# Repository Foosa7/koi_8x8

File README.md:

# Koi 8×8 — 64-channel current-source driver / readout

An open-hardware, low-cost controller for driving **TiN thermo-optic heaters on
photonic chips**: 64 independent precision current sources with per-channel
voltage readback, built from one controller board and eight hot-pluggable
8-channel analog boards.

Each daughterboard pairs a 16-bit DAC (DAC80508) with eight XTR200 precision
current sources, and reads the voltage across each load through a 6:1 divider
with a 24-bit ΔΣ ADC (AD7193), so the host gets current, voltage, resistance,
and power per channel. A Raspberry Pi Pico (RP2040) on the motherboard runs a
line-based ASCII command server over USB — one `ISETA` sets all 64 currents,
one `MEASA?` reads all 64 voltages.

## The boards

| [Motherboard](hardware/motherboard/) — RP2040 controller, 8 slots | [Daughterboard](hardware/daughterboard/) — 8 analog channels, ×8 |
| --- | --- |
|  |  |

Renders are regenerated from the KiCad boards with `kicad-cli pcb render`; each
board's own README has top, bottom, and transparent-background views.

## Key numbers

| Metric | Value |
| --- | --- |
| Channels | 64 (8 boards × 8), hot-pluggable per board |
| Current range | 0–6 mA per channel (working range 0.25–6 mA), 16-bit setting |
| Readback | 24-bit ΔΣ, divider-corrected load voltage → V / R / P per channel |
| Linearity (measured, 23 ch) | worst-case ±0.32 µA deviation from linear over 0.25–6 mA (≈0.006 % of span) |
| Offset (pre-calibration) | ≈24 µA systematic, uniform across channels; single-point cal brings it to the ±4 µA XTR200 device floor (Keithley campaign planned) |
| Full 64-channel scan | ≈11 ms/channel at the default filter rate (~0.7 s for all 64; filter rate adjustable live) |
| Parts cost | **$709 per system ≈ $11.08/channel** ([master_bom.csv](master_bom.csv)) — commercial equivalents (e.g. Qontrol) ≈ $125/channel |

## Measured results (3 boards / 24 channels, 2026-07-03)

| | |
| --- | --- |
|  |  |

Three populated daughterboards were swept 0.1–6 mA into nominal 820 Ω ±1 %
loads (one channel had no load fitted during the run and is excluded). All 23
loaded channels are linear to within ±0.32 µA and show a uniform ~24 µA
pre-calibration offset — a systematic that the planned per-channel calibration
removes. Figures are regenerated from the raw bench CSVs by
`report/figures/make_figures.py`.

## What's in this folder

| Path | Contents |
| --- | --- |
| `report/figures/` | Architecture diagram + measurement figures (and the scripts that generate them) |
| `hardware/motherboard/` | KiCad project, schematic PDF (`Schematics/`), power-tree spec (`POWER.md`), top/bottom/transparent renders, fab outputs (`production/`: gerbers, BOM, positions) |
| `hardware/daughterboard/` | Same set for the analog board, plus an interactive HTML BOM (`bom/ibom.html`) |
| `hardware/render/` | Headless KiCad → pcb2blender → Cycles pipeline for photorealistic board renders |
| `master_bom.csv` | Consolidated system BOM with unit prices and cost total |
| `firmware/motherboard-test/` | RP2040 firmware (PlatformIO, `pio run -t upload`) and Python host tools — `tools/koi_gui.py` is a live 8×8 monitor GUI; `tools/*.csv` are the raw bench datasets |
| `paper/main.pdf` | Draft HardwareX manuscript (validation section pending the calibration campaign) |

## Status (August 2026)

**In fab:** both revised boards were released to fabrication on **2026-08-12**.
The motherboard adds the protected input stage (PPTC + SMBJ16A TVS + P-FET
reverse-polarity with a BZT52C18 gate clamp), the 12 → 5 → 3.3 V tree with the
`3V3_EN` interlock, a +12 V sense divider into `GPIO26`, and the `U3.~OE`
cutover to `GPIO19`; the daughterboard adds the OPA2333 followers (U13–U16) and
their 1 kΩ series resistors. `hardware/*/production/` holds the exact gerber /
BOM / position sets that were sent.

**Done:** rev-1 hardware designed, fabricated, and brought up; firmware 1.1
with robust host protocol (auto-detection, hot-rescan, fast scanning); host GUI
and calibration tooling; all 8 daughterboards populated and tested (initial
3-board/24-channel results above — production sign-off).

**Resolved:** the ~3 mV offset seen during the 8-board test was the AD7193's
*internal* input buffer. With the 6:1 divider, a low-current channel's ADC input
sits below the buffered mode's usable common-mode range, so the buffer added a
systematic offset rather than tracking. Fixed by disabling it (`CONF.BUF = 0`)
and adding 8 external unity-gain **OPA2333** followers (U13–U16) between the
divider taps and the ADC inputs.

**Next:** Keithley 2400/2100 per-channel calibration campaign (jig designed,
parts list ready); HardwareX submission.

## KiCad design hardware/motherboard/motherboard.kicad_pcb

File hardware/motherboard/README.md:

# Motherboard — RP2040 controller board

The controller board for Koi 8×8. Carries a Raspberry Pi Pico (RP2040) and
hosts up to 8 [daughterboards](../daughterboard/) in PCIe-x4 card-edge slots,
addressing each board's DAC/ADC over a shared SPI bus. Formerly codenamed
`MOBO`. The PC talks to the Pico's firmware over USB serial — see
[`firmware/motherboard-test/`](../../firmware/motherboard-test/).

| Top | Bottom |
| --- | --- |
|  |  |

Same top view with an alpha background, for dropping onto slides or into the
paper's figures:

## What's on it

| Ref | Part | Function |
| --- | --- | --- |
| A1 | Raspberry Pi Pico (RP2040) | Runs the firmware; USB-serial host link |
| U1, U5 | SN74LV138 (74HC138) | 3-to-8 decoders — ADC/DAC chip-select across the 8 slots |
| U3 | SN74LV595 | Shift register — XTR200 front-end enables |
| U2 | TMUX1208PW | 8:1 analog mux |
| J1–J8 | Samtec PCIE-064-02-F-D-TH | 8 daughterboard slots (PCIe-x4 sockets) |
| J9–J11 | Molex 54132-5033 | 50-pin FFC connectors — channel outputs |

### Power tree

The barrel jack is the only power source; the Pico is a peripheral that cannot
run without it, enforced in hardware by the `3V3_EN` interlock (R7/R8) rather
than in firmware. Full design rationale: [`POWER.md`](POWER.md).

| Ref | Part | Function |
| --- | --- | --- |
| J12 | Barrel jack + switch pin | DC power in, 9–15 V |
| F1 | 1812L150/24MR polyfuse | Input overcurrent protection |
| D2 | SMBJ16A | Input TVS clamp (26 V clamping voltage) |
| Q1 | AO3407A | P-FET reverse-polarity protection |
| D6 | BZT52C18 | `Q1` gate–source clamp |
| U6 | K7805-500R3 | 5 V switching regulator |
| U4 | LP5912-3.3DRV | 3.3 V LDO — logic rail and daughterboard `+3V3` |
| D1 | SS34 | Feeds the Pico's VSYS from the board's 5 V rail |
| R7, R8 | 10 kΩ / 4.7 kΩ | `3V3_EN` interlock divider |
| R5, R10, C10 | 100 kΩ / 22 kΩ / 100 nF | +12 V sense divider into `GPIO26`/ADC0 (×5.5455) |

Full pricing and part numbers: [`../../master_bom.csv`](../../master_bom.csv).

## Files

| File | What it is |
| --- | --- |
| `motherboard.kicad_pro` / `.kicad_sch` / `.kicad_pcb` | The KiCad project |
| `Schematics/motherboard.pdf` | Exported schematic |
| `production/` | Fab outputs — gerbers, BOM, positions, netlist |
| `POWER.md` | Power-tree design spec — input protection chain and the `3V3_EN` interlock |
| `motherboard*.png` | Board views above, regenerated with `kicad-cli pcb render` |
| `PCIE-064-02-F-D-TH.stp`, `Pico.wrl` | 3D models used for the renders above |

Photorealistic Cycles renders (`motherboard_render*.png`) are produced by the
pipeline in [`../render/`](../render/) — not generated yet.

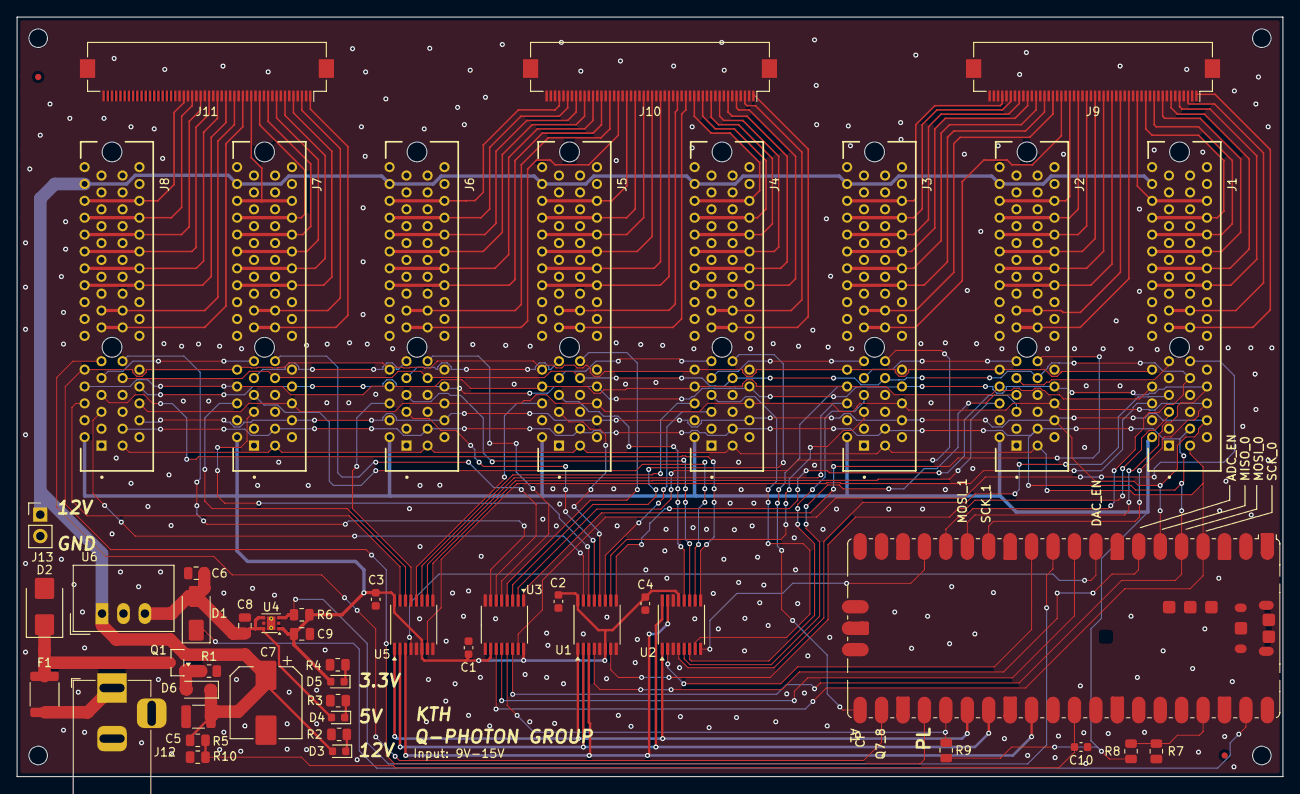
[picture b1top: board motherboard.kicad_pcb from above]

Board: 4 copper layers, 150.0 x 90.0 mm, 50 parts (0 on the bottom side), 135 nets.

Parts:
A1: RaspberryPi_Pico; RaspberryPi_Pico_SMD
C1, C2, C3, C4, C10: 0.1uF; C_0603_1608Metric
C5: 10uF; C_1210_3225Metric
C6: 22uF; C_0805_2012Metric
C7: 220uF; CP_Elec_8x10
C8, C9: 10uF; C_0805_2012Metric
D1: SS34; D_SMA
D2: SMBJ16A; D_SMB
D3, D4, D5: LED; LED_0603_1608Metric
D6: BZT52C18; D_SOD-123
F1: 1812L150/24MR; Fuse_1812_4532Metric
FID1, FID2: Fiducial; Fiducial_0.75mm_Mask1.5mm
J1, J2, J3, J4, J5, J6, J7, J8: PCIE-064-02-F-D-TH; SAMTEC_PCIE-064-02-X-D-TH
J9, J10, J11: Conn_01x50_MountingPin; Hirose_FH12-50S-0.5SH_1x50-1MP_P0.50mm_Horizontal
J12: Barrel_Jack_Switch_Pin3Ring; BarrelJack_Horizontal
J13: Conn_01x02_Pin; PinHeader_1x02_P2.54mm_Vertical
Q1: AO3407A; SOT-23
R1, R5, R6: 100k; R_0805_2012Metric
R2, R8: 4.7k; R_0805_2012Metric
R3: 1.5k; R_0805_2012Metric
R4: 680; R_0805_2012Metric
R7, R9: 10k; R_0805_2012Metric
R10: 22k; R_0805_2012Metric
U1, U5: SN74HC138PWR; TSSOP-16_4.4x5mm_P0.65mm
U2: TMUX1208PW; TSSOP-16_4.4x5mm_P0.65mm
U3: SN74LV595; TSSOP-16_4.4x5mm_P0.65mm
U4: LP5912-3.3DRV; WSON-6-1EP_2x2mm_P0.65mm_EP1x1.6mm_ThermalVias
U6: K7805-500R3; Converter_DCDC_TRACO_TSR-1_THT

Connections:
3V3_EN: A1.37 (3V3_EN), R7.2, R8.1
12V_SENSE: A1.31 (GPIO26_ADC0), C10.1, R5.2, R10.1
+3.3V: C1.1, C2.1, C3.1, C4.1, C9.1, D5.2 (A), J1.A2 (+3.3V), J2.A2 (+3.3V), J3.A2 (+3.3V), J4.A2 (+3.3V), J5.A2 (+3.3V), J6.A2 (+3.3V), J7.A2 (+3.3V), J8.A2 (+3.3V), R6.1, R8.2, R9.2, U1.6 (E2), U1.16 (VCC), U2.13 (VDD), U3.10 (~SRCLR), U3.16 (VCC), U4.1 (OUT), U5.6 (E2), U5.16 (VCC)
+5V: C6.1, C8.1, D1.2 (A), D4.2 (A), U4.4 (EN), U4.6 (IN), U6.3 (Vout)
+12V: C5.1, C7.1, D3.2 (A), D6.1 (K), J1.A30 (+12V), J2.A30 (+12V), J3.A30 (+12V), J4.A30 (+12V), J5.A30 (+12V), J6.A30 (+12V), J7.A30 (+12V), J8.A30 (+12V), J13.1, Q1.2 (S), R5.1, U6.1 (Vin)
A1: A1.26 (GPIO20), U1.1 (A0), U2.1 (A0), U5.1 (A0)
A2: A1.27 (GPIO21), U1.2 (A1), U2.16 (A1), U5.2 (A1)
A3: A1.29 (GPIO22), U1.3 (A2), U2.15 (A2), U5.3 (A2)
ADC_CS1: J1.A5 (ADC_CS), U1.7 (~Y7)
ADC_CS2: J2.A5 (ADC_CS), U1.9 (~Y6)
ADC_CS3: J3.A5 (ADC_CS), U1.10 (~Y5)
ADC_CS4: J4.A5 (ADC_CS), U1.11 (~Y4)
ADC_CS5: J5.A5 (ADC_CS), U1.12 (~Y3)
ADC_CS6: J6.A5 (ADC_CS), U1.13 (~Y2)
ADC_CS7: J7.A5 (ADC_CS), U1.14 (~Y1)
ADC_CS8: J8.A5 (ADC_CS), U1.15 (~Y0)
ADC_EN: A1.7 (GPIO5), U1.4 (~E0)
AT1: J1.A7 (AT), U2.4 (S1)
AT2: J2.A7 (AT), U2.5 (S2)
AT3: J3.A7 (AT), U2.6 (S3)
AT4: J4.A7 (AT), U2.7 (S4)
AT5: J5.A7 (AT), U2.12 (S5)
AT6: J6.A7 (AT), U2.11 (S6)
AT7: J7.A7 (AT), U2.10 (S7)
AT8: J8.A7 (AT), U2.9 (S8)
AT_EN: A1.12 (GPIO9), U2.2 (EN)
AT_MUX: A1.17 (GPIO13), U2.8 (D)
CH0: J1.A13 (CH0), J1.B13 (CH0), J9.1
CH1: J1.A15 (CH1), J1.B15 (CH1), J9.3
CH2: J1.A18 (CH2), J1.B18 (CH2), J9.5
CH3: J1.A20 (CH3), J1.B20 (CH3), J9.7
CH4: J1.A22 (CH4), J1.B22 (CH4), J9.9
CH5: J1.A24 (CH5), J1.B24 (CH5), J9.11
CH6: J1.A26 (CH6), J1.B26 (CH6), J9.13
CH7: J1.A28 (CH7), J1.B28 (CH7), J9.15
CH8: J2.A13 (CH0), J2.B13 (CH0), J9.17
CH9: J2.A15 (CH1), J2.B15 (CH1), J9.19
CH10: J2.A18 (CH2), J2.B18 (CH2), J9.21
CH11: J2.A20 (CH3), J2.B20 (CH3), J9.23
CH12: J2.A22 (CH4), J2.B22 (CH4), J9.25
CH13: J2.A24 (CH5), J2.B24 (CH5), J9.27
CH14: J2.A26 (CH6), J2.B26 (CH6), J9.29
CH15: J2.A28 (CH7), J2.B28 (CH7), J9.31
CH16: J3.A13 (CH0), J3.B13 (CH0), J9.33
CH17: J3.A15 (CH1), J3.B15 (CH1), J9.35
CH18: J3.A18 (CH2), J3.B18 (CH2), J9.37
CH19: J3.A20 (CH3), J3.B20 (CH3), J9.39
CH20: J3.A22 (CH4), J3.B22 (CH4), J9.41
CH21: J3.A24 (CH5), J3.B24 (CH5), J9.43
CH22: J3.A26 (CH6), J3.B26 (CH6), J9.45
CH23: J3.A28 (CH7), J3.B28 (CH7), J9.47
CH24: J4.A13 (CH0), J4.B13 (CH0), J10.1
CH25: J4.A15 (CH1), J4.B15 (CH1), J10.3
CH26: J4.A18 (CH2), J4.B18 (CH2), J10.5
CH27: J4.A20 (CH3), J4.B20 (CH3), J10.7
CH28: J4.A22 (CH4), J4.B22 (CH4), J10.9
CH29: J4.A24 (CH5), J4.B24 (CH5), J10.11
CH30: J4.A26 (CH6), J4.B26 (CH6), J10.13
CH31: J4.A28 (CH7), J4.B28 (CH7), J10.15
CH32: J5.A13 (CH0), J5.B13 (CH0), J10.17
CH33: J5.A15 (CH1), J5.B15 (CH1), J10.19
CH34: J5.A18 (CH2), J5.B18 (CH2), J10.21
CH35: J5.A20 (CH3), J5.B20 (CH3), J10.23
CH36: J5.A22 (CH4), J5.B22 (CH4), J10.25
CH37: J5.A24 (CH5), J5.B24 (CH5), J10.27
CH38: J5.A26 (CH6), J5.B26 (CH6), J10.29
CH39: J5.A28 (CH7), J5.B28 (CH7), J10.31
CH40: J6.A13 (CH0), J6.B13 (CH0), J10.33
CH41: J6.A15 (CH1), J6.B15 (CH1), J10.35
CH42: J6.A18 (CH2), J6.B18 (CH2), J10.37
CH43: J6.A20 (CH3), J6.B20 (CH3), J10.39
CH44: J6.A22 (CH4), J6.B22 (CH4), J10.41
CH45: J6.A24 (CH5), J6.B24 (CH5), J10.43
CH46: J6.A26 (CH6), J6.B26 (CH6), J10.45
CH47: J6.A28 (CH7), J6.B28 (CH7), J10.47
CH48: J7.A13 (CH0), J7.B13 (CH0), J11.1
CH49: J7.A15 (CH1), J7.B15 (CH1), J11.3
CH50: J7.A18 (CH2), J7.B18 (CH2), J11.5
CH51: J7.A20 (CH3), J7.B20 (CH3), J11.7
CH52: J7.A22 (CH4), J7.B22 (CH4), J11.9
CH53: J7.A24 (CH5), J7.B24 (CH5), J11.11
CH54: J7.A26 (CH6), J7.B26 (CH6), J11.13
CH55: J7.A28 (CH7), J7.B28 (CH7), J11.15
CH56: J8.A13 (CH0), J8.B13 (CH0), J11.17
CH57: J8.A15 (CH1), J8.B15 (CH1), J11.19
CH58: J8.A18 (CH2), J8.B18 (CH2), J11.21
CH59: J8.A20 (CH3), J8.B20 (CH3), J11.23
CH60: J8.A22 (CH4), J8.B22 (CH4), J11.25
CH61: J8.A24 (CH5), J8.B24 (CH5), J11.27
CH62: J8.A26 (CH6), J8.B26 (CH6), J11.29
CH63: J8.A28 (CH7), J8.B28 (CH7), J11.31
CP: A1.21 (GPIO16), J1.A8 (A0_MUX), J2.A8 (A0_MUX), J3.A8 (A0_MUX), J4.A8 (A0_MUX), J5.A8 (A0_MUX), J6.A8 (A0_MUX), J7.A8 (A0_MUX), J8.A8 (A0_MUX)
DAC_CS1: J1.A6 (DAC_CS), U5.7 (~Y7)
DAC_CS2: J2.A6 (DAC_CS), U5.9 (~Y6)
DAC_CS3: J3.A6 (DAC_CS), U5.10 (~Y5)
DAC_CS4: J4.A6 (DAC_CS), U5.11 (~Y4)
DAC_CS5: J5.A6 (DAC_CS), U5.12 (~Y3)
DAC_CS6: J6.A6 (DAC_CS), U5.13 (~Y2)
DAC_CS7: J7.A6 (DAC_CS), U5.14 (~Y1)
DAC_CS8: J8.A6 (DAC_CS), U5.15 (~Y0)
DAC_EN: A1.9 (GPIO6), U5.4 (~E0)
GND: A1.3 (GND), A1.8 (GND), A1.13 (GND), A1.18 (GND), A1.23 (GND), A1.28 (GND), A1.33 (AGND), A1.38 (GND), A1.D2 (GND), C1.2, C2.2, C3.2, C4.2, C5.2, C6.2, C7.2, C8.2, C9.2, C10.2, D2.2 (A2), J1.A1 (~PRSNT1), J1.A3 (GND), J1.A4 (GND), J1.A9 (A1_MUX), J1.A12 (GND), J1.A14 (CH0), J1.A16 (CH1), J1.A17 (GND), J1.A19 (CH2), J1.A21 (CH3), J1.A23 (CH4), J1.A25 (CH5), J1.A27 (CH6), J1.A29 (CH7), J1.A31 (GND), J1.B2 (GND), J1.B5 (GND), J1.B7 (GND), J1.B10 (GND), J1.B12 (GND), J1.B14 (CH0), J1.B16 (CH1), J1.B19 (CH2), J1.B21 (CH3), J1.B23 (CH4), J1.B25 (CH5), J1.B27 (CH6), J1.B29 (CH7), J1.B31 (~PRSNT2), J1.B32 (GND), J2.A1 (~PRSNT1), J2.A3 (GND), J2.A4 (GND), J2.A12 (GND), J2.A14 (CH0), J2.A16 (CH1), J2.A17 (GND), J2.A19 (CH2), J2.A21 (CH3), J2.A23 (CH4), J2.A25 (CH5), J2.A27 (CH6), J2.A29 (CH7), J2.A31 (GND), J2.B2 (GND), J2.B5 (GND), J2.B7 (GND), J2.B10 (GND), J2.B12 (GND), J2.B14 (CH0), J2.B16 (CH1), J2.B19 (CH2), J2.B21 (CH3), J2.B23 (CH4), J2.B25 (CH5), J2.B27 (CH6), J2.B29 (CH7), J2.B31 (~PRSNT2), J2.B32 (GND), J3.A1 (~PRSNT1), J3.A3 (GND), J3.A4 (GND), J3.A12 (GND), J3.A14 (CH0), J3.A16 (CH1), J3.A17 (GND), J3.A19 (CH2), J3.A21 (CH3), J3.A23 (CH4), J3.A25 (CH5), J3.A27 (CH6), J3.A29 (CH7), J3.A31 (GND), J3.B2 (GND), J3.B5 (GND), J3.B7 (GND), J3.B10 (GND), J3.B12 (GND), J3.B14 (CH0), J3.B16 (CH1), J3.B19 (CH2), J3.B21 (CH3), J3.B23 (CH4), J3.B25 (CH5), J3.B27 (CH6), J3.B29 (CH7), J3.B31 (~PRSNT2), J3.B32 (GND), J4.A1 (~PRSNT1), J4.A3 (GND), J4.A4 (GND), J4.A12 (GND), J4.A14 (CH0), J4.A16 (CH1), J4.A17 (GND), J4.A19 (CH2), J4.A21 (CH3), J4.A23 (CH4), J4.A25 (CH5), J4.A27 (CH6), J4.A29 (CH7), J4.A31 (GND), J4.B2 (GND), J4.B5 (GND), J4.B7 (GND), J4.B10 (GND), J4.B12 (GND), J4.B14 (CH0), J4.B16 (CH1), J4.B19 (CH2), J4.B21 (CH3), J4.B23 (CH4), J4.B25 (CH5), J4.B27 (CH6), J4.B29 (CH7), J4.B31 (~PRSNT2), J4.B32 (GND), J5.A1 (~PRSNT1), J5.A3 (GND), J5.A4 (GND), J5.A12 (GND), J5.A14 (CH0), J5.A16 (CH1), J5.A17 (GND), J5.A19 (CH2), J5.A21 (CH3), J5.A23 (CH4), J5.A25 (CH5), J5.A27 (CH6), J5.A29 (CH7), J5.A31 (GND), J5.B2 (GND), J5.B5 (GND), J5.B7 (GND), J5.B10 (GND), J5.B12 (GND), J5.B14 (CH0), J5.B16 (CH1), J5.B19 (CH2), J5.B21 (CH3), J5.B23 (CH4), J5.B25 (CH5), J5.B27 (CH6), J5.B29 (CH7), J5.B31 (~PRSNT2), J5.B32 (GND), J6.A1 (~PRSNT1), J6.A3 (GND), J6.A4 (GND), J6.A12 (GND), J6.A14 (CH0), J6.A16 (CH1), J6.A17 (GND), J6.A19 (CH2), J6.A21 (CH3), J6.A23 (CH4), J6.A25 (CH5), J6.A27 (CH6), J6.A29 (CH7), J6.A31 (GND), J6.B2 (GND), J6.B5 (GND), J6.B7 (GND), J6.B10 (GND), J6.B12 (GND), J6.B14 (CH0), J6.B16 (CH1), J6.B19 (CH2), J6.B21 (CH3), J6.B23 (CH4), J6.B25 (CH5), J6.B27 (CH6), J6.B29 (CH7), J6.B31 (~PRSNT2), J6.B32 (GND), J7.A1 (~PRSNT1), J7.A3 (GND), J7.A4 (GND), J7.A12 (GND), J7.A14 (CH0), J7.A16 (CH1), J7.A17 (GND), J7.A19 (CH2), J7.A21 (CH3), J7.A23 (CH4), J7.A25 (CH5), J7.A27 (CH6), J7.A29 (CH7), J7.A31 (GND), J7.B2 (GND), J7.B5 (GND), J7.B7 (GND), J7.B10 (GND), J7.B12 (GND), J7.B14 (CH0), J7.B16 (CH1), J7.B19 (CH2), J7.B21 (CH3), J7.B23 (CH4), J7.B25 (CH5), J7.B27 (CH6), J7.B29 (CH7), J7.B31 (~PRSNT2), J7.B32 (GND), J8.A1 (~PRSNT1), J8.A3 (GND), J8.A4 (GND), J8.A12 (GND), J8.A14 (CH0), J8.A16 (CH1), J8.A17 (GND), J8.A19 (CH2), J8.A21 (CH3), J8.A23 (CH4), J8.A25 (CH5), J8.A27 (CH6), J8.A29 (CH7), J8.A31 (GND), J8.B2 (GND), J8.B5 (GND), J8.B7 (GND), J8.B10 (GND), J8.B12 (GND), J8.B14 (CH0), J8.B16 (CH1), J8.B19 (CH2), J8.B21 (CH3), J8.B23 (CH4), J8.B25 (CH5), J8.B27 (CH6), J8.B29 (CH7), J8.B31 (~PRSNT2), J8.B32 (GND), J9.2, J9.4, J9.6, J9.8, J9.10, J9.12, J9.14, J9.16, J9.18, J9.20, J9.22, J9.24, J9.26, J9.28, J9.30, J9.32, J9.34, J9.36, J9.38, J9.40, J9.42, J9.44, J9.46, J9.48, J9.49, J9.50, J9.MP (MountPin), J10.2, J10.4, J10.6, J10.8, J10.10, J10.12, J10.14, J10.16, J10.18, J10.20, J10.22, J10.24, J10.26, J10.28, J10.30, J10.32, J10.34, J10.36, J10.38, J10.40, J10.42, J10.44, J10.46, J10.48, J10.49, J10.50, J10.MP (MountPin), J11.2, J11.4, J11.6, J11.8, J11.10, J11.12, J11.14, J11.16, J11.18, J11.20, J11.22, J11.24, J11.26, J11.28, J11.30, J11.32, J11.MP (MountPin), J12.2, J12.3, J13.2, R1.2, R2.1, R3.1, R4.1, R7.1, R10.2, U1.5 (~E1), U1.8 (GND), U2.3 (VSS), U2.14 (GND), U3.8 (GND), U4.5 (GND), U4.7 (EP), U5.5 (~E1), U5.8 (GND), U6.2 (GND)
MISO_0: A1.6 (GPIO4), J1.B4 (MISO_0), J2.B4 (MISO_0), J3.B4 (MISO_0), J4.B4 (MISO_0), J5.B4 (MISO_0), J6.B4 (MISO_0), J7.B4 (MISO_0), J8.B4 (MISO_0)
MISO_1: A1.16 (GPIO12), J1.B9 (MISO_1), J2.B9 (MISO_1), J3.B9 (MISO_1), J4.B9 (MISO_1), J5.B9 (MISO_1), J6.B9 (MISO_1), J7.B9 (MISO_1), J8.B9 (MISO_1)
MOSI_0: A1.5 (GPIO3), J1.B3 (MOSI_0), J2.B3 (MOSI_0), J3.B3 (MOSI_0), J4.B3 (MOSI_0), J5.B3 (MOSI_0), J6.B3 (MOSI_0), J7.B3 (MOSI_0), J8.B3 (MOSI_0), U3.14 (SER)
MOSI_1: A1.15 (GPIO11), J1.B8 (MOSI_1), J2.B8 (MOSI_1), J3.B8 (MOSI_1), J4.B8 (MOSI_1), J5.B8 (MOSI_1), J6.B8 (MOSI_1), J7.B8 (MOSI_1), J8.B8 (MOSI_1)
unnamed: D2.1 (A1), F1.1, Q1.3 (D)
unnamed: D3.1 (K), R2.2
unnamed: D4.1 (K), R3.2
unnamed: D5.1 (K), R4.2
unnamed: D6.2 (A), Q1.1 (G), R1.1
PG: A1.11 (GPIO8), R6.2, U4.3 (PG)
PL: A1.24 (GPIO18), J1.A10 (A2_MUX), J2.A10 (A2_MUX), J3.A10 (A2_MUX), J4.A10 (A2_MUX), J5.A10 (A2_MUX), J6.A10 (A2_MUX), J7.A10 (A2_MUX), J8.A10 (A2_MUX)
Q7_1: J1.A11 (~PERST), J2.A9 (A1_MUX)
Q7_2: J2.A11 (~PERST), J3.A9 (A1_MUX)
Q7_3: J3.A11 (~PERST), J4.A9 (A1_MUX)
Q7_4: J4.A11 (~PERST), J5.A9 (A1_MUX)
Q7_5: J5.A11 (~PERST), J6.A9 (A1_MUX)
Q7_6: J6.A11 (~PERST), J7.A9 (A1_MUX)
Q7_7: J7.A11 (~PERST), J8.A9 (A1_MUX)
Q7_8: A1.22 (GPIO17), J8.A11 (~PERST)
SCK_0: A1.4 (GPIO2), J1.B1 (SCK_0), J2.B1 (SCK_0), J3.B1 (SCK_0), J4.B1 (SCK_0), J5.B1 (SCK_0), J6.B1 (SCK_0), J7.B1 (SCK_0), J8.B1 (SCK_0), U3.11 (SRCLK)
SCK_1: A1.14 (GPIO10), J1.B6 (SCK_1), J2.B6 (SCK_1), J3.B6 (SCK_1), J4.B6 (SCK_1), J5.B6 (SCK_1), J6.B6 (SCK_1), J7.B6 (SCK_1), J8.B6 (SCK_1)
VIN_JACK: F1.2, J12.1
VSYS: A1.39 (VSYS), D1.1 (K)
XTR_OD_1: J1.B11 (~PERST), U3.15 (QA)
XTR_OD_2: J2.B11 (~PERST), U3.1 (QB)
XTR_OD_3: J3.B11 (~PERST), U3.2 (QC)
XTR_OD_4: J4.B11 (~PERST), U3.3 (QD)
XTR_OD_5: J5.B11 (~PERST), U3.4 (QE)
XTR_OD_6: J6.B11 (~PERST), U3.5 (QF)
XTR_OD_7: J7.B11 (~PERST), U3.6 (QG)
XTR_OD_8: J8.B11 (~PERST), U3.7 (QH)
XTR_RCLK: A1.10 (GPIO7), U3.12 (RCLK)
~OE: A1.25 (GPIO19), R9.1, U3.13 (~OE)

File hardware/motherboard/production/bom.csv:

Designator,Footprint,Quantity,Value,LCSC Part #
A1,RaspberryPi_Pico_SMD,1,RaspberryPi_Pico,C7203003
"C1, C10, C2, C3, C4",0603,5,0.1uF,C14663
C5,1210,1,10uF,C77102
C6,0805,1,22uF,C45783
C7,CP_Elec_8x10,1,220uF,C125981
"C8, C9",0805,2,10uF,C84416
D1,D_SMA,1,SS34,C8678
D2,D_SMB,1,SMBJ16A,C151254
"D3, D4, D5",0603,3,LED,C157740
D6,D_SOD-123,1,BZT52C18,C192739
F1,1812,1,1812L150/24MR,C142805
"J1, J2, J3, J4, J5, J6, J7, J8",SAMTEC_PCIE-064-02-X-D-TH,8,PCIE-064-02-F-D-TH,C4597619
"J10, J11, J9",Hirose_FH12-50S-0.5SH_1x50-1MP_P0.50mm_Horizontal,3,Conn_01x50_MountingPin,C202116
J12,BarrelJack_Horizontal,1,Barrel_Jack_Switch_Pin3Ring,C84007
J13,PinHeader_1x02_P2.54mm_Vertical,1,Conn_01x02_Pin,C32713268
Q1,SOT-23,1,AO3407A,C15155
"R1, R5, R6",0805,3,100k,C96346
R10,0805,1,22k,C114565
"R2, R8",0805,2,4.7k,C431850
R3,0805,1,1.5k,C4310
R4,0805,1,680,C17798
"R7, R9",0805,2,10k,C84376
"U1, U5",TSSOP-16_4.4x5mm_P0.65mm,2,SN74HC138PWR,C157527
U2,TSSOP-16_4.4x5mm_P0.65mm,1,TMUX1208PW,C494728
U3,TSSOP-16_4.4x5mm_P0.65mm,1,SN74LV595,C116847
U4,WSON-6-1EP_2x2mm_P0.65mm_EP1x1.6mm_ThermalVias,1,LP5912-3.3DRV,C524780
U6,Converter_DCDC_TRACO_TSR-1_THT,1,K7805-500R3,C19188491
